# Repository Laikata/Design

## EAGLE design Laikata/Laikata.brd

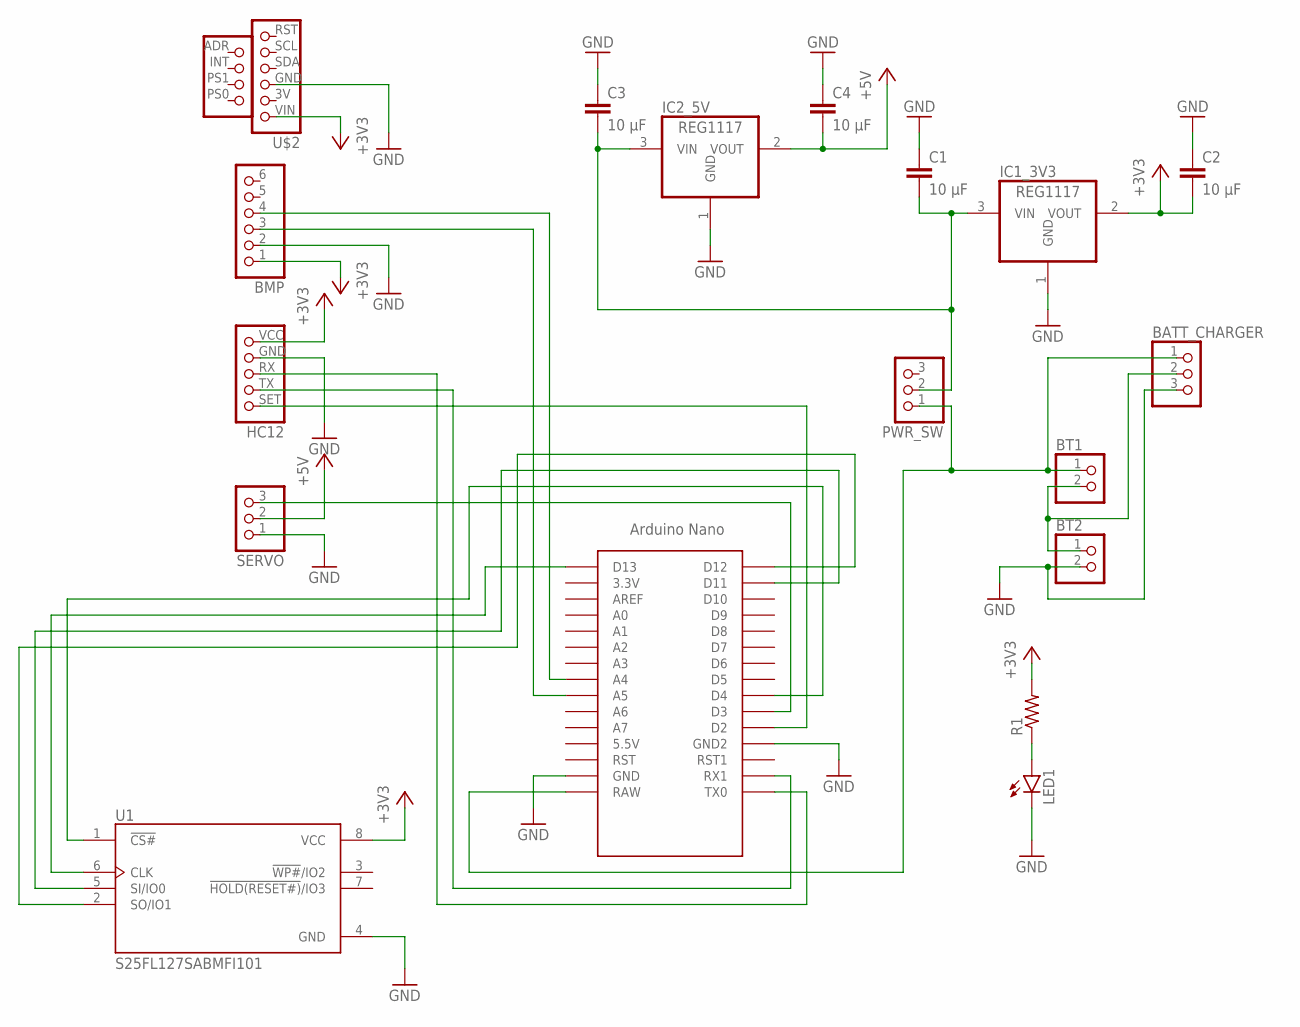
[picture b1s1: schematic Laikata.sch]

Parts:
BATT_CHARGER: PINHD-1X3; 1X03
BMP: PINHD-1X6; 1X06
BT1, BT2: PINHD-1X2; 1X02
C1, C2, C3, C4: 10 μF; C1210
HC12: HC12
IC1_3V3, IC2_5V: REG1117; SOT223
LED1: LED3MM
PWR_SW: PINHD-1X3; 1X03
R1: R-US_R1206; R1206
SERVO: PINHD-1X3; 1X03
U1: S25FL127SABMFI101; SOIC127P800X216-8N
U$1: NANO
U$2: IMU

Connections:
+3V3: BMP.1, C2.2, HC12.VCC, IC1_3V3.2 (VOUT), R1.2, U1.8 (VCC), U$2.VIN
+5V: C4.2, IC2_5V.2 (VOUT), SERVO.2
GND: BATT_CHARGER.3, BMP.2, BT2.2, C1.1, C2.1, C3.1, C4.1, HC12.GND, IC1_3V3.1 (GND), IC2_5V.1 (GND), LED1.K (C), SERVO.1, U1.4 (GND), U$1.GND, U$1.GND1 (GND2), U$2.GND
unnamed: BATT_CHARGER.1, BT1.1, PWR_SW.1, U$1.RAW
unnamed: C1.2, C3.2, IC1_3V3.3 (VIN), IC2_5V.3 (VIN), PWR_SW.2
unnamed: HC12.SET, U$1.D2
unnamed: HC12.TX, U$1.RX1
unnamed: HC12.RX, U$1.TX0
unnamed: SERVO.3, U$1.D3
unnamed: LED1.A, R1.1
unnamed: U1.1 (!CS#), U$1.D4
unnamed: U1.6 (CLK), U$1.D13
unnamed: U1.5 (SI/IO0), U$1.D11
unnamed: U1.2 (SO/IO1), U$1.D12
unnamed: BMP.3, U$1.A5
unnamed: BMP.4, U$1.A4
unnamed: BATT_CHARGER.2, BT1.2, BT2.1

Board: 2 copper layers, 18 parts (0 on the bottom side), 17 nets, no tracks yet.

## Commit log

2023-03-20 PCB
    First commit
2023-03-20 IMU component
    Created and added a custom component for the BNO055 sensor
2023-03-22 Upload CDR
2023-03-23 CDR Parte Pepe
    He añadido mi parte del CDR donde se incluye el diseño mecánico
2023-03-23 CDR Yeray
    paracaidas y extension de varios apartados como la introduccion y plan de difusión
2023-03-28 CDR Josep
2023-03-28 Parte estacion de base
2023-03-28 CDR provisional 1
    Le falta rellenar información y las misiones
2023-03-29 Presupuesto
    El presupuesto provisional sin acabar
2023-03-29 CDRProvisional2
    Falta las misiones. 8 páginas
2023-03-29 CDR Parte Pepe 2
    Añadido la nueva parte de Pepe del CDR
2023-03-29 CDR Yeray v2
    add images
2023-03-29 CDRYeray v2
    add diagrama de flujos
2023-03-30 CDR Bien Maquetado No acabado 1
    El nombre es muy esplicito
2023-03-31 CDR Bien Maquetado No Acabado 2
    La segunda parte
2023-03-31 CDR Bien Maquetado No acabado 3
    Y ahora es una saga
2023-03-31 Retocando
2023-03-31 Añadir diagrama y extender misión secundaria
2023-04-25 Se ha organizado el repositorio Design y se han añadido el diseño mecánico final y el CDR final.
2023-04-25 Update README.txt
    Arreglos realizados en la maquetación del README.txt
